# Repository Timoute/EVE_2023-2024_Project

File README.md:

# Cahier des charges Gants 

## Objectif General
- Contrôle de robot
    - Mouvement
        - Mecanique
        - " peau artificiel "
    - Contraction Muscle
    - Orientation de la main
    - Contact des doigts
    - Haptic feedback (potentiometre)
## Pour qui ?
Doit pouvoir être utilisé par une personne sans handicape 

## Présentation du projet
Objectif général : Contrôler un robot avec un gant 
Objectifs spécifiques :
- Feedback
- Réception des signaux musculaires 
- Retour sur l’orientation - position du robot
- Piloter la main avec le gant ou avoir des actions spécifiques pour chaque mouvement fait avec le gant. 
    
## Description des besoin
Besoins fonctionnels :  
- feedback réception des signaux musculaires 
- retour sur l’orientation 
- position du robot 
- piloter la main avec le gant ou avoir des actions spécifiques pour chaque mouvement fait avec le gant. 
                        
Besoins non fonctionnels : ergonomie, sécurité 

## Contraintes
Contraintes techniques : ROS, Python, C, Arduino IDE, Velostat

Contraintes budgétaires : 

Contraintes temporelles : Janvier 2024.

## Spécifications détaillées
Architecture : décrivez la structure générale du projet.

Interfaces : Cube IDE, VS Code, ROS

Bases de données : décrivez les besoins en matière de stockage et de gestion des données.

## Critères d'acceptation
- Énumérez les conditions qui doivent être remplies pour que le projet soit considéré comme réussi :
- Avoir un gant fonctionnel et ergonomique
- Acquérir des signaux en fonctions de différentes actions de la main ( mouvement des doigts, contraction des muscles, orientation de la main…)
- Avoir une communication stable 

## Liste des capteurs
- Electromyogram :
    - https://www.gotronic.fr/art-capteur-emg-sen0240-27861.htm
    - https://eu.robotshop.com/fr/products/electromyography-emg-sensor
    - https://www.mouser.fr/ProductDetail/SparkFun/DEV-18425?qs=t7xnP681wgWy3U1F8u8yVw%3D%3D&mgh=1&vip=1&gclid=CjwKCAjwgsqoBhBNEiwAwe5w0-L5xPd-VuEDQAtsSe9MgerAB8_JgHJxVIk0EnzZVOSmlyj8zlm68BoCh2wQAvD_BwE
    - https://www.gotronic.fr/art-capteur-pour-muscle-myoware-2-0-36900.htm
- Gyroscope, accélerometre, magnétomètre, capteur d'orientation : sans PCB : https://www.mouser.fr/ProductDetail/TDK-InvenSense/MPU-9250?qs=u4fy%2FsgLU9OhGjFkQSZssA%3D%3D
  avec PCB : https://www.amazon.fr/9250-Module-Acc%C3%A9l%C3%A9rom%C3%A8tre-Gyroscope-magn%C3%A9tom%C3%A8tre-Raspberry/dp/B01M74J70A
- Velostat(artificial skin): to capture pressure, twist
- Pressure sensor: to capture the contact between two fingers: https://www.gotronic.fr/art-capteur-de-force-fsr01-11552.htm
- Potentiometer: to capture finger bending
    Potentiometre linéaire x5: https://www.mouser.fr/ProductDetail/Bourns/PTA2043-2015CIB203?qs=AQlKX63v8RsiU3Md8%2FQpDw%3D%3D

- INSPIRATION
- https://www.youtube.com/watch?v=xNSRmXKSI_4
- https://fr.farnell.com/adafruit-industries/1361/accessory-type-conductive-sheet/dp/2419170?gclid=CjwKCAjwsKqoBhBPEiwALrrqiDeGaSW_4uc-rm59poSZfxalWY5j2dFrcLATg-_UMGxAqV16yRr28hoCB38QAvD_BwE&mckv=_dc|pcrid||plid||kword||match||slid||product|2419170|pgrid||ptaid||&CMP=KNC-GFR-GEN-SHOPPING-Catch-All-Geo-Split-Control-12-July-23&gross_price=true

  video : https://www.youtube.com/watch?v=nHVNF83Se9k

Pourquoi celui la ? 

Pour mettre une image : 

https://github.com/someone-eng/LeapMotion-remote-controlling-robot-hand

MYOWare
https://cdn.sparkfun.com/assets/learn_tutorials/1/9/5/6/MyoWare_v2_QuickStartGuide.pdf
https://github.com/sparkfun/SparkFun_MyoWare_Code_Examples
https://microcontrollerslab.com/force-sensor-fsr-arduino-tutorial/

## To Order
- STM32 : https://www.mouser.fr/ProductDetail/STMicroelectronics/STM32G474RET6?qs=PzGy0jfpSMvUBs7PMTDqlg%3D%3D&mgh=1&vip=1&gclid=Cj0KCQjwj5mpBhDJARIsAOVjBdp6-F5e4-ACCbXfp7QWk2OJl_ML0-fUJPXXJXP-bVWwRIPgl04Lvd4aAoJjEALw_wcB

### RS Component

### Wurth Elektronik

### Mouser Electronics

# Base de Données pour IA
Fait avec le Leap Motion
https://www.kaggle.com/datasets/gti-upm/leapgestrecog/

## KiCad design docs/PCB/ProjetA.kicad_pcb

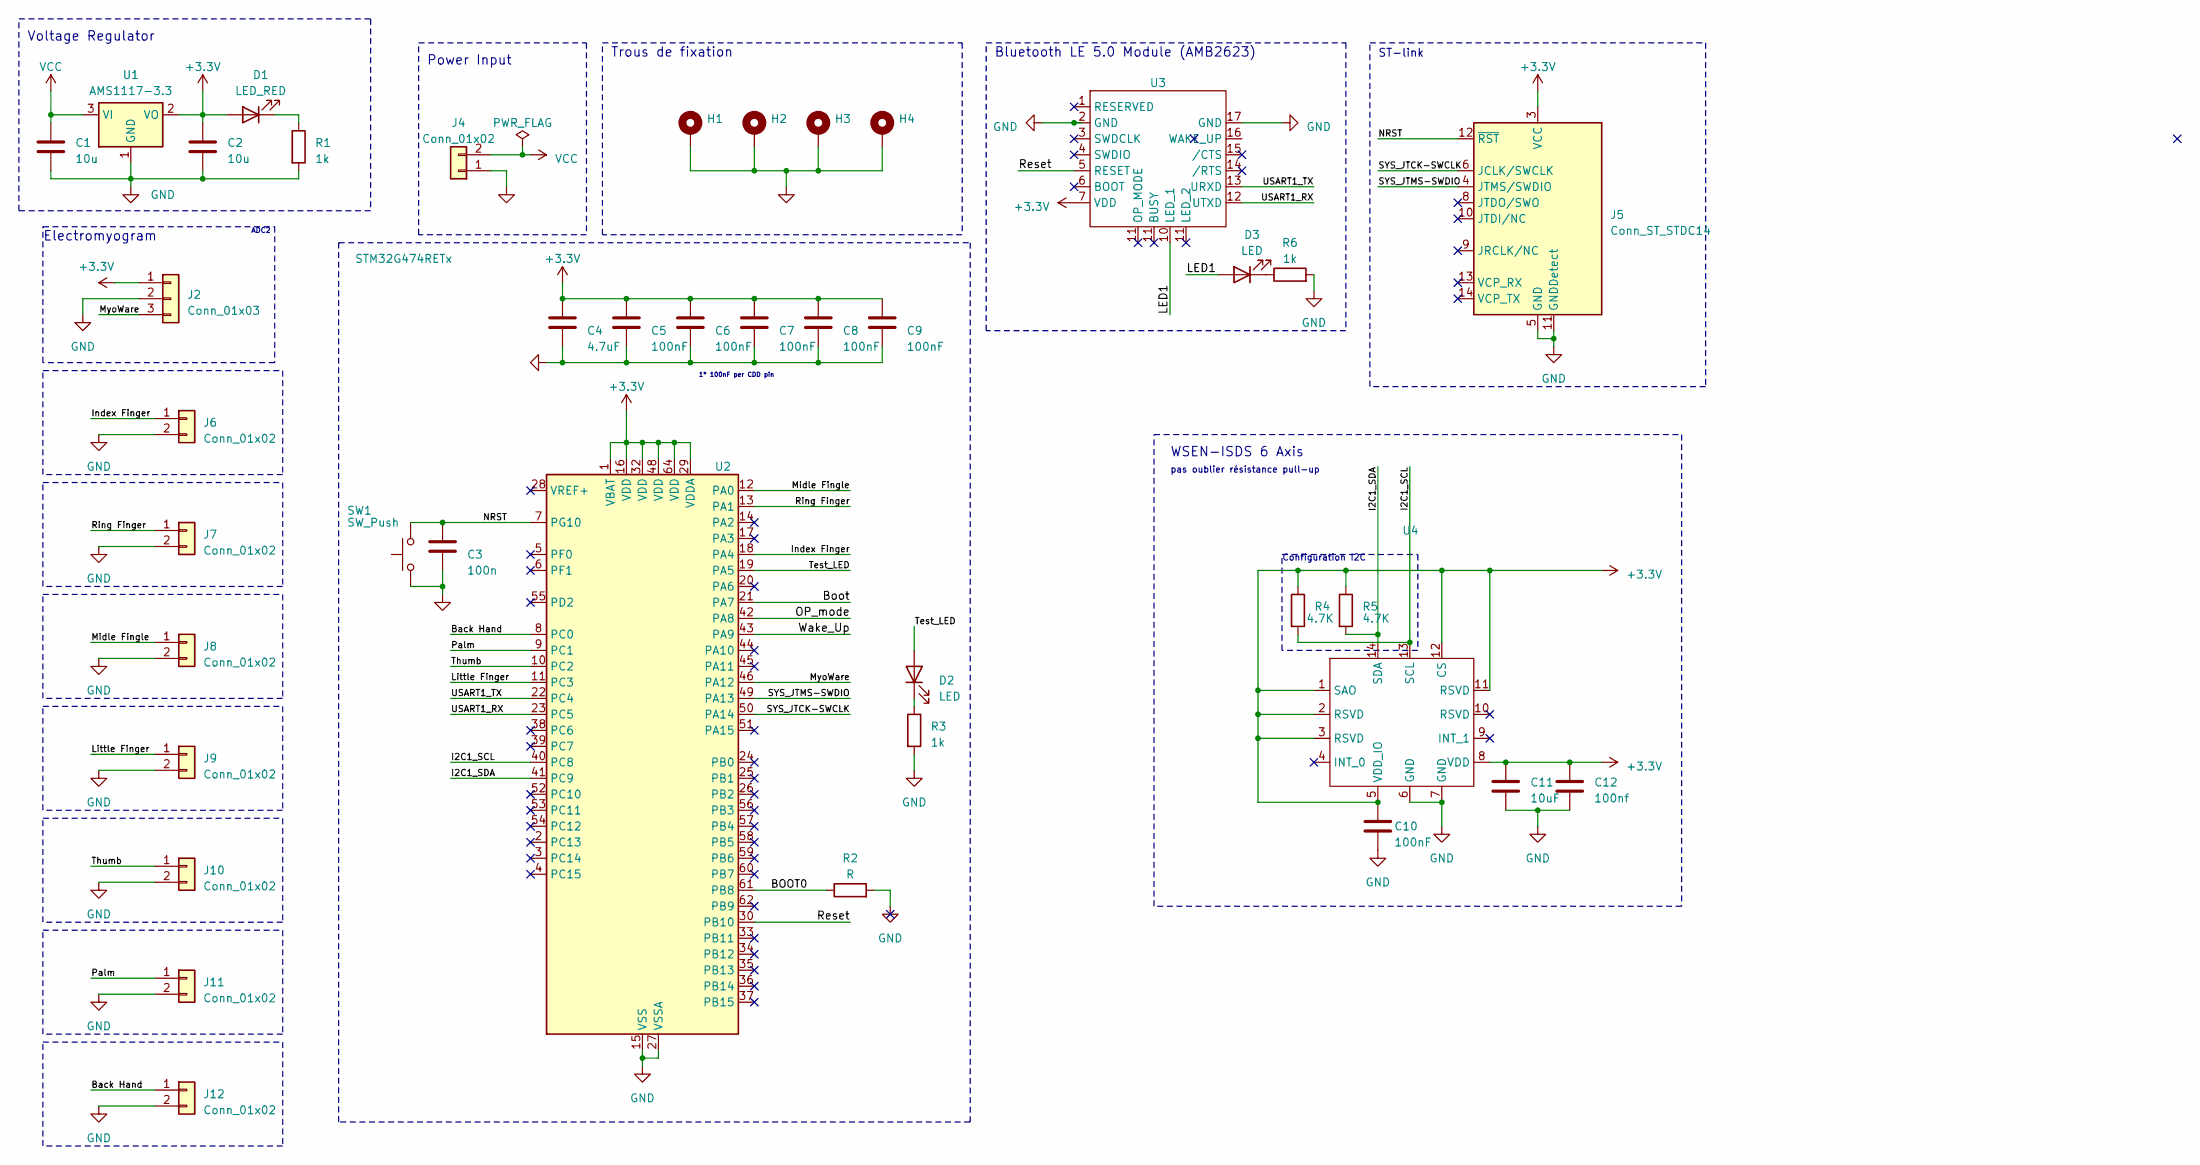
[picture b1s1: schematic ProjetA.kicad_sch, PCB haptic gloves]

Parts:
C1, C2: 10u; C_0603_1608Metric_Pad1.08x0.95mm_HandSolder
C3: 100n; C_0603_1608Metric_Pad1.08x0.95mm_HandSolder
C4: 4.7uF; C_0603_1608Metric_Pad1.08x0.95mm_HandSolder
C5, C6, C7, C8, C9, C10: 100nF; C_0603_1608Metric_Pad1.08x0.95mm_HandSolder
C11: 10uF; C_0603_1608Metric_Pad1.08x0.95mm_HandSolder
C12: 100nf; C_0603_1608Metric_Pad1.08x0.95mm_HandSolder
D1: LED_RED; LED_0603_1608Metric_Pad1.05x0.95mm_HandSolder
D2, D3: LED; LED_0603_1608Metric_Pad1.05x0.95mm_HandSolder
H1, H2, H3, H4: MountingHole_Pad; MountingHole_2.7mm_Pad_Via
J2: Conn_01x03; JST_XH_B3B-XH-A_1x03_P2.50mm_Vertical
J4: Conn_01x02; JST_XH_B2B-XH-A_1x02_P2.50mm_Vertical
J5: Conn_ST_STDC14; PinHeader_2x07_P1.27mm_Vertical_SMD
J6, J7, J8, J9, J10, J11, J12: Conn_01x02; JST_XH_S2B-XH-A_1x02_P2.50mm_Horizontal
R1, R3, R6: 1k; R_1206_3216Metric_Pad1.30x1.75mm_HandSolder
R2: R; R_1206_3216Metric_Pad1.30x1.75mm_HandSolder
R4, R5: 4.7K; R_1206_3216Metric_Pad1.30x1.75mm_HandSolder
SW1: SW_Push; SW_SPST_B3U-1000P
U1: AMS1117-3.3; SOT-223-3_TabPin2
U2: STM32G474RETx; LQFP-64_10x10mm_P0.5mm
U3: Proteus-II (Bluetooth)
U4: WSEN-ISDS 6 Axis IMU

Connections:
+3.3V: C2.2, C4.1, C5.1, C6.1, C7.1, C8.1, C9.1, C10.1, C11.1, C12.1, D1.2 (A), J2.1, J5.3 (VCC), R4.1, R5.1, U1.2 (VO), U2.1 (VBAT), U2.16 (VDD), U2.29 (VDDA), U2.32 (VDD), U2.48 (VDD), U2.64 (VDD), U3.7 (VDD), U4.1 (SAO), U4.2 (RSVD), U4.3 (RSVD), U4.5 (VDD_IO), U4.8 (VDD), U4.11 (RSVD), U4.12 (CS)
/BOOT0: R2.1, U2.61 (PB8)
/Back Hand: J12.1, U2.8 (PC0)
/Boot: U2.21 (PA7)
/I2C1_SCL: R4.2, U2.40 (PC8), U4.13 (SCL)
/I2C1_SDA: R5.2, U2.41 (PC9), U4.14 (SDA)
/Index Finger: J6.1, U2.18 (PA4)
/LED1: D3.2 (A), U3.10 (LED_1)
/Little Finger: J9.1, U2.11 (PC3)
/Midle Fingle: J8.1, U2.12 (PA0)
/MyoWare: J2.3, U2.46 (PA12)
/NRST: C3.1, J5.12 (~RST), SW1.2, U2.7 (PG10)
/OP_mode: U2.42 (PA8)
/Palm: J11.1, U2.9 (PC1)
/Reset: U2.30 (PB10), U3.5 (RESET)
/Ring Finger: J7.1, U2.13 (PA1)
/SYS_JTCK-SWCLK: J5.6 (JCLK/SWCLK), U2.50 (PA14)
/SYS_JTMS-SWDIO: J5.4 (JTMS/SWDIO), U2.49 (PA13)
/Test_LED: D2.2 (A), U2.19 (PA5)
/Thumb: J10.1, U2.10 (PC2)
/USART1_RX: U2.23 (PC5), U3.12 (UTXD)
/USART1_TX: U2.22 (PC4), U3.13 (URXD)
/Wake_Up: U2.43 (PA9)
GND: C1.1, C2.1, C3.2, C4.2, C5.2, C6.2, C7.2, C8.2, C9.2, C10.2, C11.2, C12.2, H1.1, H2.1, H3.1, H4.1, J2.2, J4.1, J5.5 (GND), J5.7 (GND), J5.11 (GNDDetect), J6.2, J7.2, J8.2, J9.2, J10.2, J11.2, J12.2, R1.2, R2.2, R3.2, R6.2, SW1.1, U1.1 (GND), U2.15 (VSS), U2.27 (VSSA), U2.31 (VSS), U2.47 (VSS), U2.63 (VSS), U3.2 (GND), U3.17 (GND), U4.6 (GND), U4.7 (GND)
unnamed: D1.1 (K), R1.1
unnamed: D2.1 (K), R3.1
unnamed: D3.1 (K), R6.1
VCC: C1.2, J4.2, U1.3 (VI)

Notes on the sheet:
Voltage Regulator
1* 100nF per CDD pin
Configuration I2C
Trous de fixation
ST-link
pas oublier résistance pull-up
ADC2
WSEN-ISDS 6 Axis
Bluetooth LE 5.0 Module (AMB2623)
Electromyogram
Power Input

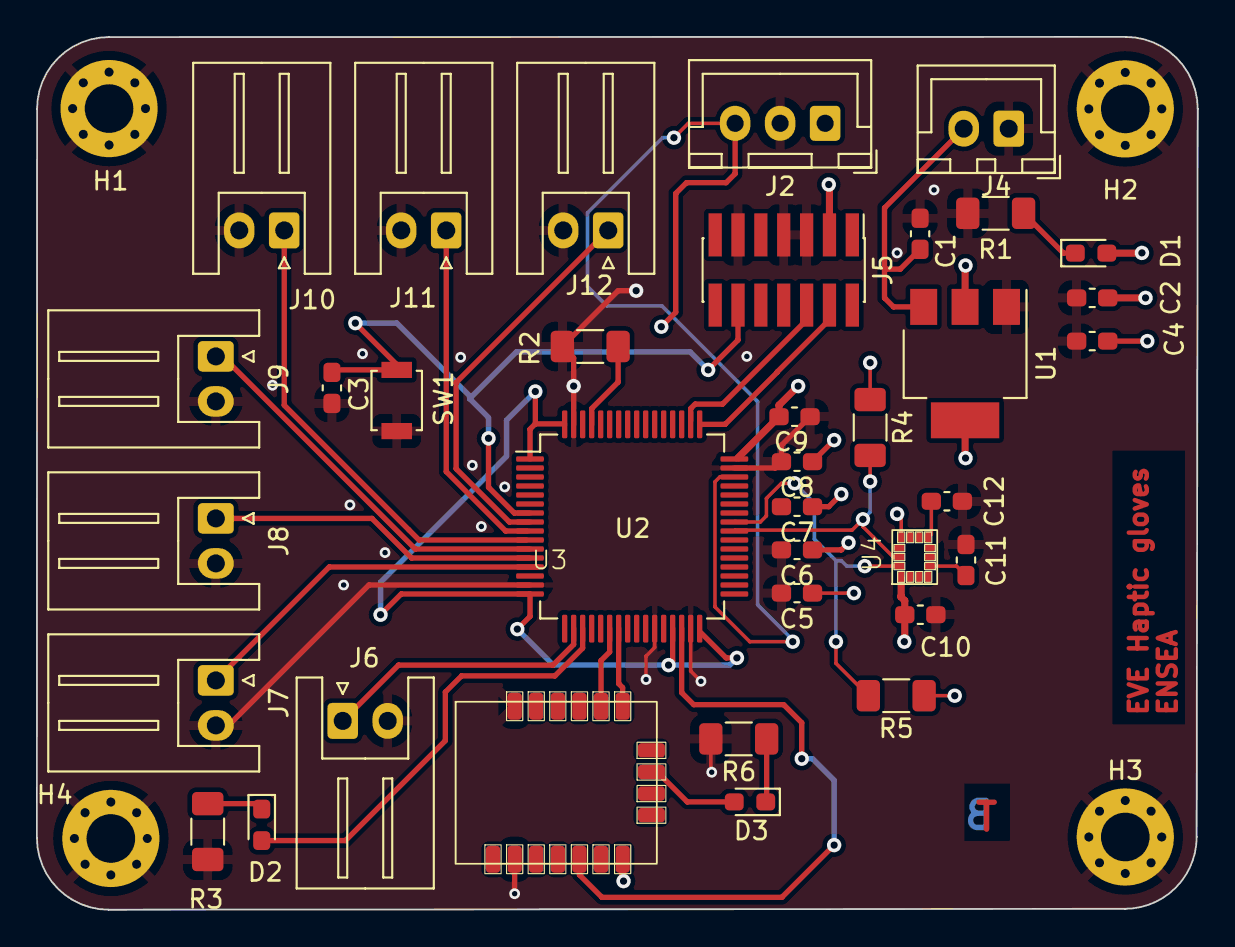
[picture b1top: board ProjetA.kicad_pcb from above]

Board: 4 copper layers, 64.5 x 48.5 mm, 40 parts (0 on the bottom side), 25 nets.

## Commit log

2023-11-22 Create KiCad
    KiCad Files
2023-11-22 KiCad Files
2024-01-09 Créé avec Colaboratory
